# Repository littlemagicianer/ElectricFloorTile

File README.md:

# Piezoelectric Energy-Harvesting Floor Tile

This project is a piezoelectric floor tile designed to generate electrical energy from footsteps. When a person steps on the tile, a 3D-printed PETG flexing plate transfers and distributes the force to piezoelectric elements underneath. The generated electrical signal is rectified into DC power, conditioned through an energy-harvesting circuit, and stored in a battery.

The system also measures the harvested voltage and provides the user with real-time voltage readings. The project combines mechanical design, piezoelectric energy harvesting, power electronics, PCB design, embedded sensing, and 3D printing to explore how everyday human motion can be converted into usable electrical energy.

The tile itself is hot-swappable, meaning that the user can change the surface to whatever texture they want, whether it be a turf surface, hardwood flooring, etc. This allows for the tile to be used in a large variety of applications.

When looking at the images of the CAD, there are 3 main elements to the physical design: the hot-swappable plate, which is held in by M4 screws; the PETG flexion plate to aid the transfer of energy to the piezos; and the TPU flexible padding/ PLA sidewalls to stop overflexion of the PETG plate.

The electrical system has 4 main elements: the rectifier circuit to change AC output from the piezos to DC, the battery backup, a buck converter to USB-C ports, and the ESP-32 voltage logging.

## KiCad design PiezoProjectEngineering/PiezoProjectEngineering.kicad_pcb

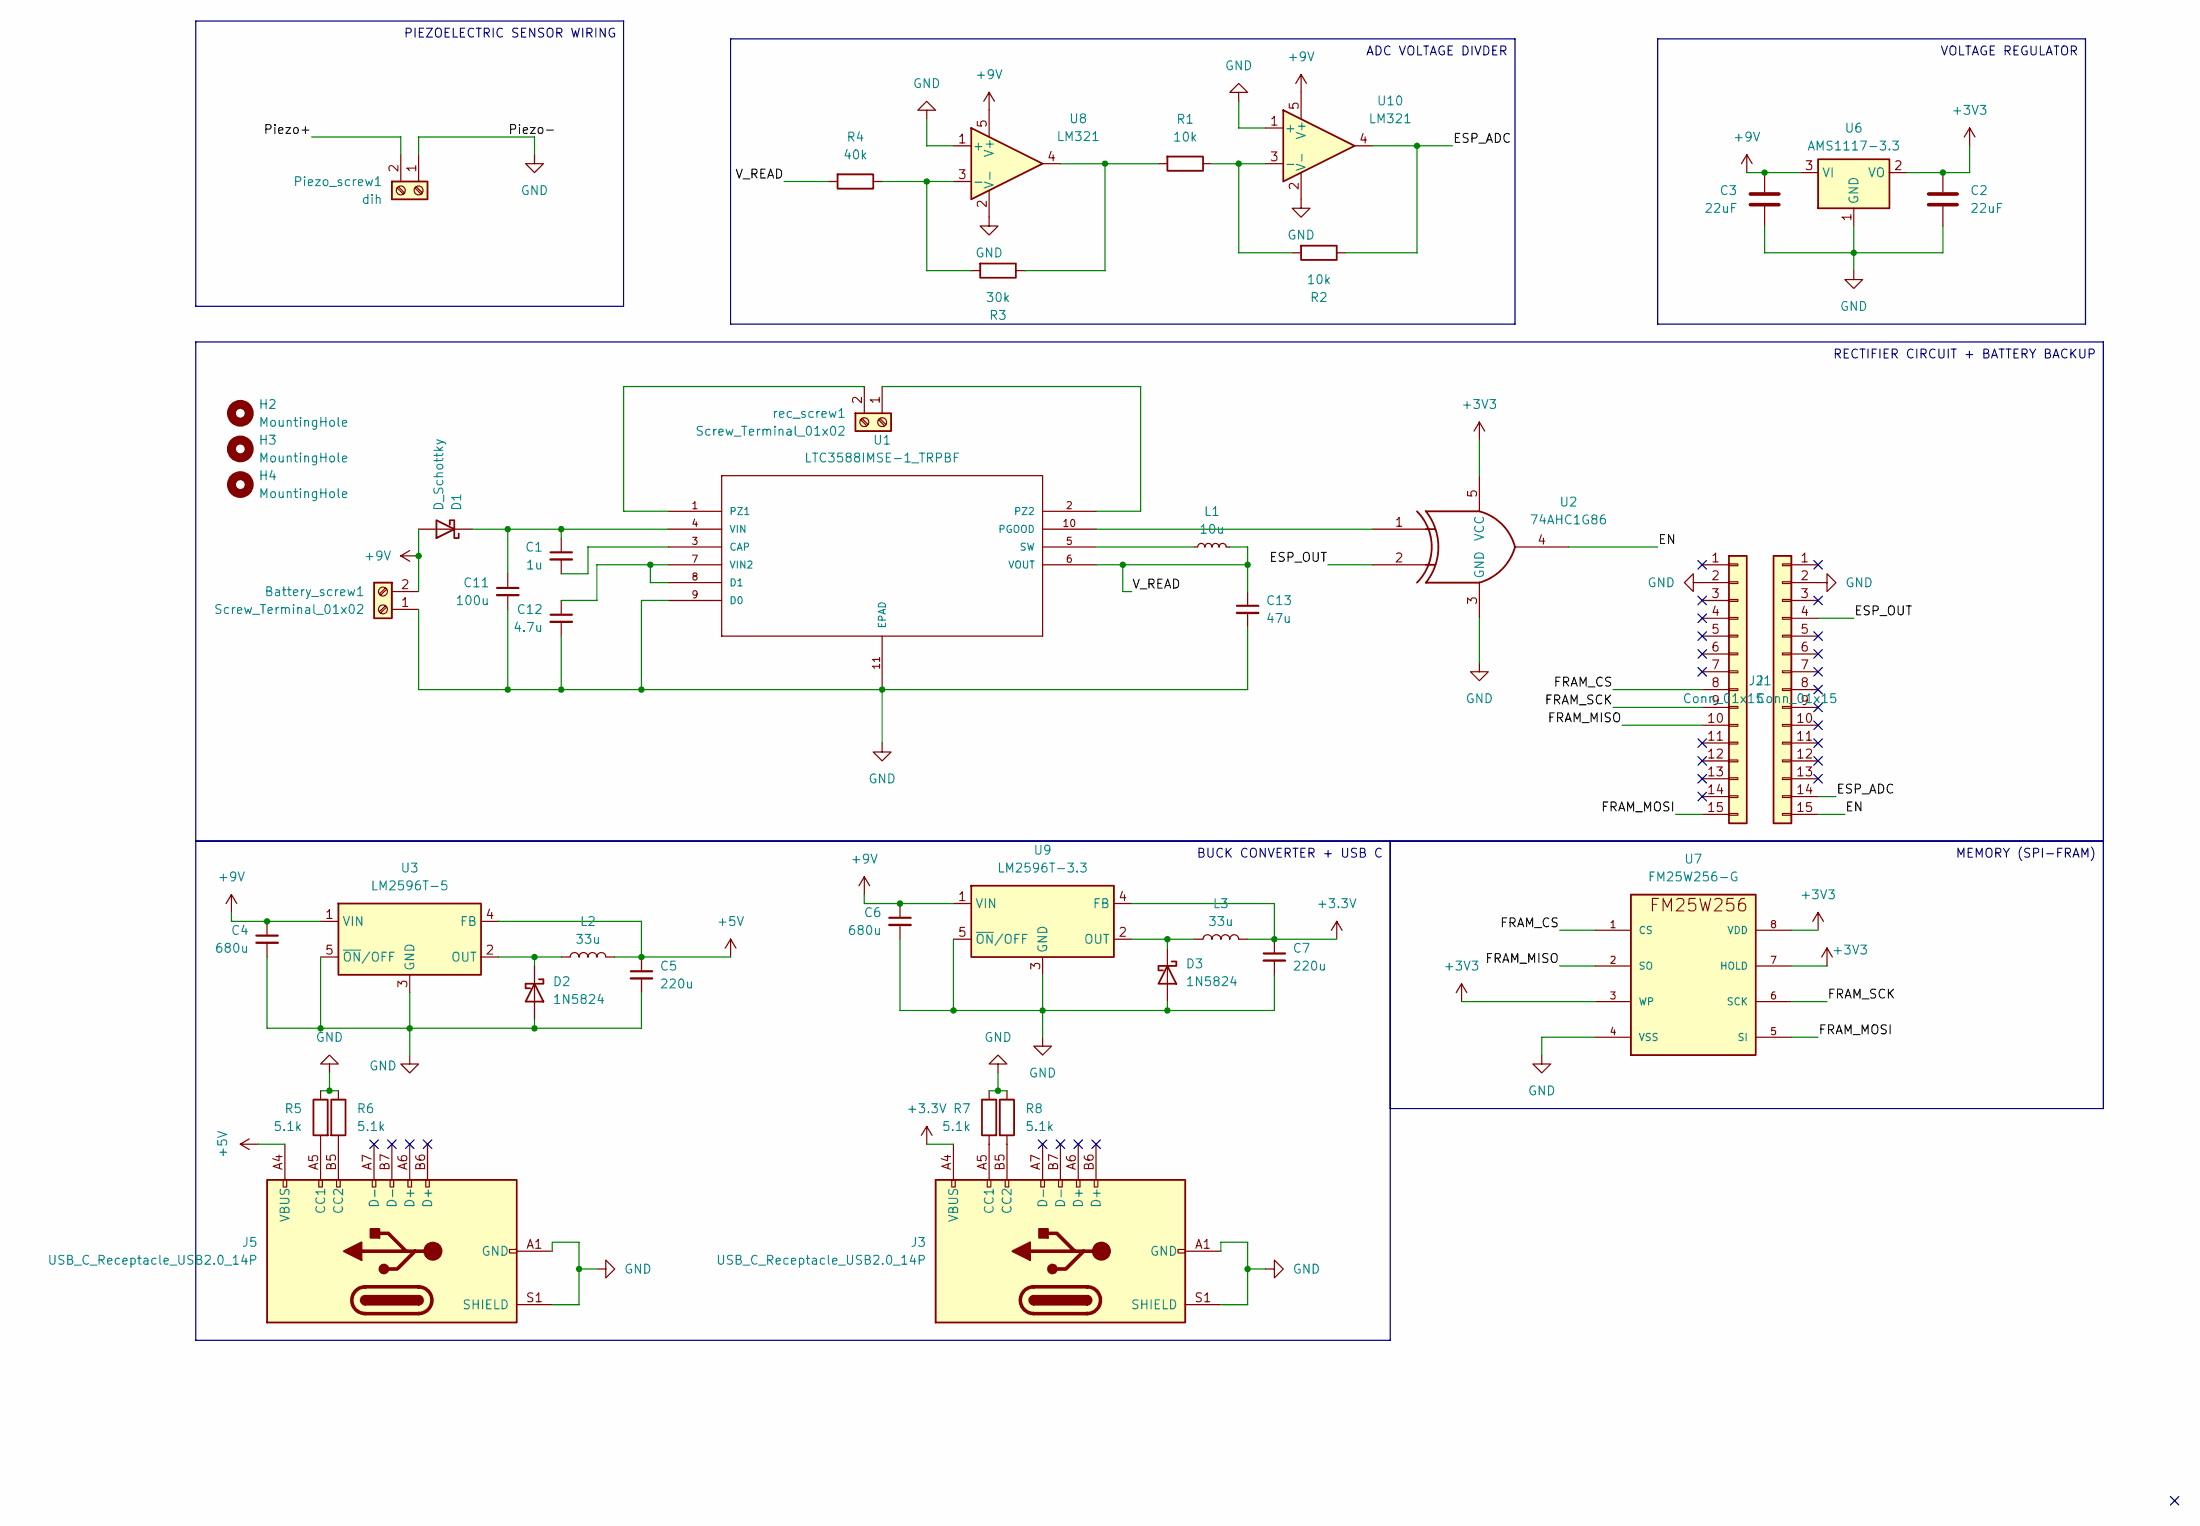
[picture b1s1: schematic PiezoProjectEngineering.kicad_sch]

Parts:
Battery_screw1: Screw_Terminal_01x02; AMASS_XT30UPB-M_1x02_P5.0mm_Vertical
C1: 1u; C_0603_1608Metric
C2, C3: 22uF; C_1206_3216Metric
C4, C6: 680u; CP_Elec_10x10
C5, C7: 220u; CP_Elec_10x10.5
C11: 100u; CP_Elec_10x10.5
C12: 4.7u; C_1206_3216Metric
C13: 47u; C_1206_3216Metric
D1: D_Schottky; D_SOD-323F
D2, D3: 1N5824; D_SMA
H2, H3, H4: MountingHole; MountingHole_4.3mm_M4
J1, J2: Conn_01x15; TE_1-640454-5
J3, J5: USB_C_Receptacle_USB2.0_14P; USB_C_Receptacle_GCT_USB4105-xx-A_16P_TopMnt_Horizontal
L1: 10u; L_Bourns_SRP7028A_7.3x6.6mm
L2, L3: 33u; L_Bourns_SRR1260
Piezo_screw1: dih
R1, R2: 10k; R_0603_1608Metric
R3: 30k; R_0603_1608Metric
R4: 40k; R_0805_2012Metric
R5, R6, R7, R8: 5.1k; R_0603_1608Metric
U1: LTC3588IMSE-1_TRPBF; MSOP-10_MSE; MANUFACTURER_PART_NUMBER ltc3588imse1#pbf
U2: 74AHC1G86; SOT-23-5
U3: LM2596T-5; TO-220-5_P3.4x3.7mm_StaggerOdd_Lead3.8mm_Vertical
U6: AMS1117-3.3; SOT-223-3_TabPin2
U7: FM25W256-G; SOIC8
U8, U10: LM321; SOT-23-5
U9: LM2596T-3.3; TO-220-5_P3.4x3.7mm_StaggerOdd_Lead3.8mm_Vertical
rec_screw1: Screw_Terminal_01x02; AMASS_XT30UPB-M_1x02_P5.0mm_Vertical

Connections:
+3.3V: C7.1, J3.A4 (VBUS), J3.A9 (VBUS), J3.B4 (VBUS), J3.B9 (VBUS), L3.2, U9.4 (FB)
+3V3: C2.1, U2.5 (VCC), U6.2 (VO), U7.3 (WP), U7.7 (HOLD), U7.8 (VDD)
+5V: C5.1, J5.A4 (VBUS), J5.A9 (VBUS), J5.B4 (VBUS), J5.B9 (VBUS), L2.2, U3.4 (FB)
+9V: Battery_screw1.2 (Pin_1), C3.1, C4.1, C6.1, D1.2 (A), U3.1 (VIN), U6.3 (VI), U8.5 (V+), U9.1 (VIN), U10.5 (V+)
/EN: J2.15, U2.4
/ESP_ADC: J2.14, R2.1, U10.4
/ESP_OUT: J2.4, U2.2
/FRAM_CS: J1.8, U7.1 (CS)
/FRAM_MISO: J1.10, U7.2 (SO)
/FRAM_MOSI: J1.15, U7.5 (SI)
/FRAM_SCK: J1.9, U7.6 (SCK)
/V_READ: C13.1, L1.2, R4.2, U1.6 (VOUT)
GND: Battery_screw1.1 (Pin_2), C2.2, C3.2, C4.2, C5.2, C6.2, C7.2, C11.2, C12.2, C13.2, D2.2 (A), D3.2 (A), J1.2, J2.2, J3.A1 (GND), J3.A12 (GND), J3.B1 (GND), J3.B12 (GND), J3.S1 (SHIELD), J5.A1 (GND), J5.A12 (GND), J5.B1 (GND), J5.B12 (GND), J5.S1 (SHIELD), Piezo_screw1.1 (Pin_2), R5.1, R6.1, R7.1, R8.1, U1.9 (D0), U1.11 (EPAD), U2.3 (GND), U3.3 (GND), U3.5 (~ON/OFF), U6.1 (GND), U7.4 (VSS), U8.1 (+), U8.2 (V-), U9.3 (GND), U9.5 (~ON/OFF), U10.1 (+), U10.2 (V-)
unnamed: C1.1, C11.1, D1.1 (K), U1.4 (VIN)
unnamed: D2.1 (K), L2.1, U3.2 (OUT)
unnamed: D3.1 (K), L3.1, U9.2 (OUT)
unnamed: J3.A5 (CC1), R7.2
unnamed: J3.B5 (CC2), R8.2
unnamed: J5.A5 (CC1), R5.2
unnamed: J5.B5 (CC2), R6.2
unnamed: R1.2, R3.1, U8.4
unnamed: C1.2, U1.3 (CAP)
unnamed: C12.1, U1.7 (VIN2), U1.8 (D1)
unnamed: U1.10 (PGOOD), U2.1
unnamed: U1.1 (PZ1), rec_screw1.2 (Pin_1)
unnamed: U1.2 (PZ2), rec_screw1.1 (Pin_2)
unnamed: L1.1, U1.5 (SW)
unnamed: R3.2, R4.1, U8.3 (-)
unnamed: R1.1, R2.2, U10.3 (-)

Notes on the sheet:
BUCK CONVERTER + USB C
PIEZOELECTRIC SENSOR WIRING
VOLTAGE REGULATOR
ADC VOLTAGE DIVDER
RECTIFIER CIRCUIT + BATTERY BACKUP
MEMORY (SPI-FRAM)

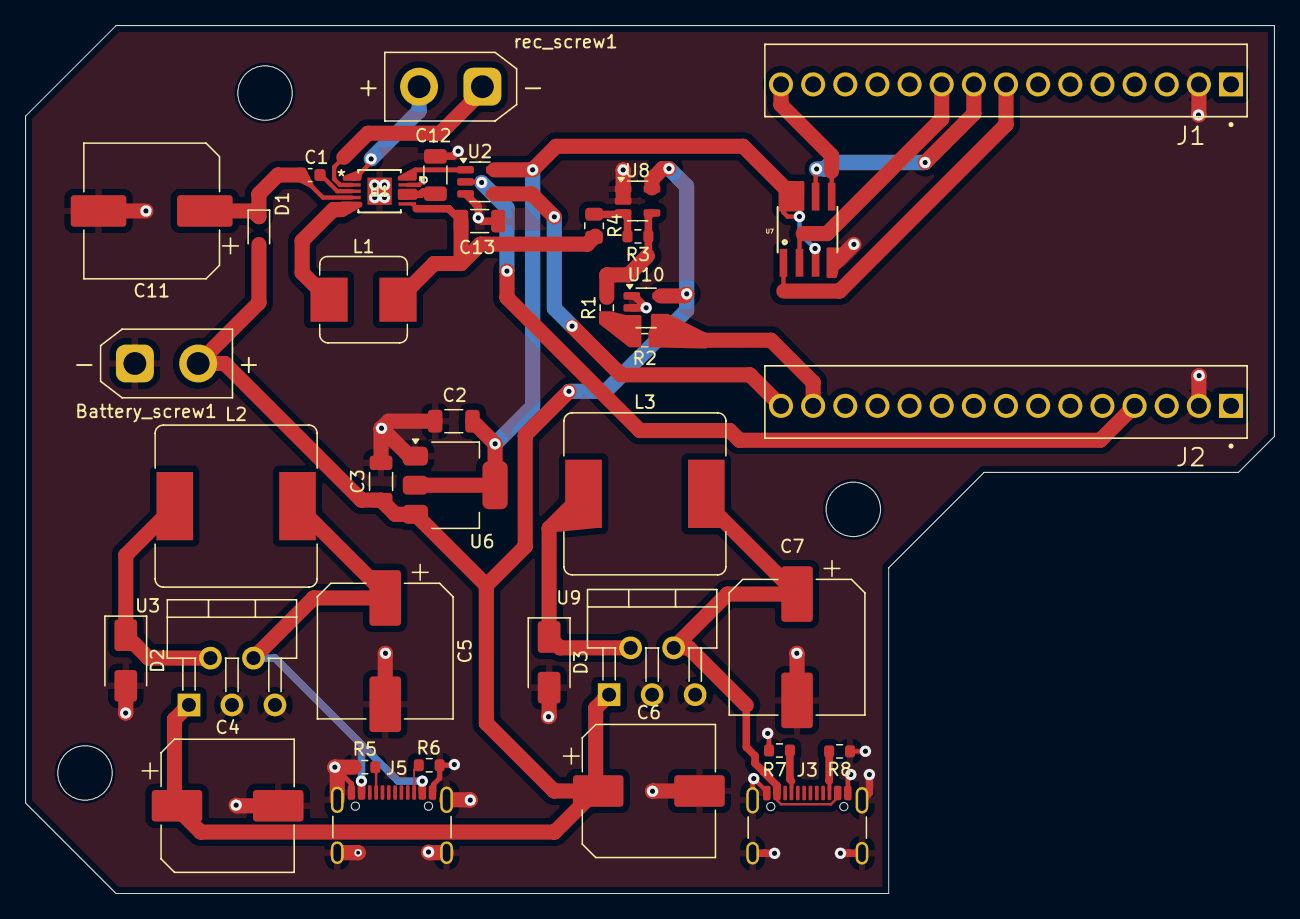
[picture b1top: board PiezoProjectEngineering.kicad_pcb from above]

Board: 2 copper layers, 98.7 x 68.6 mm, 41 parts (0 on the bottom side), 29 nets.

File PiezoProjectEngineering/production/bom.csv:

Designator,Footprint,Quantity,Value,LCSC Part #
"BATTERY_SCREW1, REC_SCREW1",AMASS_XT30UPB-M_1x02_P5.0mm_Vertical,2,Screw_Terminal_01x02,
C1,0603,1,1u,C696901
C11,CP_Elec_10x10.5,1,100u,C88801
C12,1206,1,4.7u,C277508
C13,1206,1,47u,C68361
"C2, C3",1206,2,22uF,C513771
"C4, C6",CP_Elec_10x10,2,680u,C164080
"C5, C7",CP_Elec_10x10.5,2,220u,C131159
D1,D_SOD-323F,1,D_Schottky,C369937
"D2, D3",D_SMA,2,1N5824,C22452
"J1, J2",TE_1-640454-5,2,Conn_01x15,C7509525
"J3, J5",USB_C_Receptacle_GCT_USB4105-xx-A_16P_TopMnt_Horizontal,2,USB_C_Receptacle_USB2.0_14P,C3020560
L1,L_Bourns_SRP7028A_7.3x6.6mm,1,10u,C2041441
"L2, L3",L_Bourns_SRR1260,2,33u,C2042435
"R1, R2",0603,2,10k,C25804
R3,0603,1,30k,C22984
R4,0805,1,40k,C5266069
"R5, R6, R7, R8",0603,4,5.1k,C23186
U1,MSOP-10_MSE,1,LTC3588IMSE-1_TRPBF,C685122
"U10, U8",SOT-23-5,2,LM321,C131103
U2,SOT-23-5,1,74AHC1G86,C402161
U3,TO-220-5_P3.4x3.7mm_StaggerOdd_Lead3.8mm_Vertical,1,LM2596T-5,C22386545
U6,SOT-223-3_TabPin2,1,AMS1117-3.3,C6186
U7,SOIC8,1,FM25W256-G,C23520
U9,TO-220-5_P3.4x3.7mm_StaggerOdd_Lead3.8mm_Vertical,1,LM2596T-3.3,C1355424
